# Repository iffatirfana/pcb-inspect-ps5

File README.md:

# Fabric Inspection Assistant (Raspberry Pi 5, fully offline)

Bharat AI-SoC Challenge 2026-27, Problem Statement 5: real-time industrial defect detection and quality-control assistant.
Entry: textile and fabric quality control on a Raspberry Pi 5 (CPU only), with Llama 3.2 1B running through ExecuTorch.

## What it does

One photo goes in; a verdict, a repair route and a short three-line operator note come out, with no cloud connection.

```
photo / webcam -> YOLOv8n-seg detector (onnxruntime) -> rule engine (severity, verdict)
              -> [only if nothing found] anomaly second opinion (ResNet18 + normal-patch bank)
              -> Llama 3.2 1B on ExecuTorch (Risk / Check / Action note) -> dashboard + SQLite log
```

- **Detector:** finds Hole, Knot, Line and Stain defects, with polygon and area.
- **Anomaly second opinion:** when the detector finds nothing, a second model compares the photo with a memory bank of normal-denim patches (ResNet18 layer2+layer3 features, nearest-neighbour distance, PatchCore-style). If more than 1.5% of the photo looks abnormal, the verdict becomes **REVIEW** with up to three regions marked "Anomaly". It can only raise PASS to REVIEW; it never causes REWORK or REJECT, and it does not run when the detector already found a defect. The dashboard shows an **anomaly heatmap** card (per-pixel score, flag threshold outlined) for these photos.
- **Rule engine:** Low / Medium / High severity from area, then PASS / REVIEW / REWORK / REJECT. Only rules decide the verdict.
- **Rule-generated recommendations:** disposition, urgency, repair route, what to check and likely cause per defect (`kb/fabric_guidance.yaml`).
- **Llama advisor:** writes three lines (Risk, Check, Action) from the verdict, findings and SOP line, using a ~300-token chat-template prompt with one worked example. Its reply is validated: it must not say release/ship/approve for a non-PASS verdict, and every number must come from the facts it was given. On any failure, after one retry, a template built from the SOP is used. Skipped on PASS.
- **Dashboard:** local web page with a colour verdict banner, annotated photo, findings table, recommendations, the Llama note, the anomaly heatmap when the second opinion fires, timings, operator feedback and history.
- **Log:** every inspection is stored in SQLite (`fabric_inspections`).

Vision runs on the Pi CPU (onnxruntime). Llama runs on the Arm CPU through ExecuTorch. No Hailo accelerator is used.

## Measured results (Raspberry Pi 5, 16 GB, our own photos of blue denim)

| Measurement | Value |
| --- | --- |
| Detector time | 583 ms (about 1.7 FPS, 960 px input) |
| Photo to verdict | 0.99 s median |
| Llama advice, persistent runner | 7 to 14 s per reply (16 tokens per second) |
| Peak memory | Python 226 MB + Llama runner 731 MB (0.96 GB of 16 GB) |
| False alarms at confidence 0.5 | 0 of 71 normal photos |
| Hole recall at confidence 0.5 | 12 of 15 |
| Thread (Line) recall at confidence 0.5, detector alone | 2 of 6 (weak) |

### Anomaly second opinion (held-out photos, same denim fabric)

The memory bank was built from the 51 train photos only. The pixel threshold was chosen on the 10 validation photos only. The test normals and all defect photos were never used for building or tuning. Run through the full pipeline (laptop CPU, about 0.38 s per photo):

| Set | Result |
| --- | --- |
| Validation normals (10) | 10 PASS (threshold set here) |
| Test normals (10) | 8 PASS, 2 REVIEW (false alarms) |
| Holes (15) | detector alone 12 REJECT; with second opinion 15 of 15 flagged (3 as REVIEW) |
| Threads (6) | detector alone 2 REJECT; with second opinion 6 of 6 flagged (4 as REVIEW) |

These are small sets from one fabric and one camera setup, so they show the idea works but are not an accuracy claim. On the Pi the anomaly step took about 0.76 s on a clean photo (full clean-photo run 1.11 s). Full pipeline, fresh process: hole photo REJECT with model-written advice in 5.09 s including model load; two consecutive requests to the persistent runner ran without reload.

## Pattern cloth: missing-motif check

`fabric_pattern.py` looks for a missing printed motif on repeating-print cloth (fabric key `pattern`). It finds the
print grid in one photo and flags a position that has a motif on both sides but almost no printed ink.
It needs no reference photo and never gives more than REVIEW.

| Test | Result |
|---|---|
| 30 synthetic missing motifs (made from normal photos) | 27 found at the right place |
| 14 clean photos not used to build the rule | 1 flagged (1 false gap) |

Limits: the missing motifs are synthetic and the clean photos show only a few cloth positions, so treat the
numbers as an estimate. Wrong-type or flipped motifs are not detected (the hand-printed motifs vary too much).
It works only on a regular repeating print. A reference-photo comparison was tried first and rejected: it
flagged 6 of 14 clean photos because the cloth layout differs between areas. A DINOv2 Siamese model from the
team was also tested; alone it flags too many regions on clean cloth, so it is not in the pipeline.

## Limitations

- The anomaly second opinion is trained on normal blue denim only and flags about 2 in 10 held-out normal photos for a quick manual check. It is advisory: it can raise PASS to REVIEW and nothing more.
- Trained on blue denim only. A yellow patterned cloth gave false Holes, and on grey cloth and in shadows the anomaly second opinion flags regions (REVIEW only); other fabrics need new data or a bank built from clean photos of that fabric.
- The pixel-to-mm scale in `kb/fabric.yaml` (`px_per_mm`) comes from a ruler photo and is valid only for that camera, height and image size; redo it if the setup changes. If `calibrated` is false the dashboard warns that sizes and severities are estimates.
- The older `..._512.pte` file measured only about 127 tokens of usable context on the Pi. The rebuilt `llama3_2_1b_q8da4w_ctx512.pte` was tested on the Pi with prompts of 7, 213 and 469 tokens (469 + 42 generated = 511). `config.yaml` caps prompt plus reply at 480 tokens; the advice prompt is about 300 tokens.
- Experiments that did not help (tiling, a larger 960x960 detector) are described in the technical report.

## Repository layout (fabric entry)

| Path | Purpose |
| --- | --- |
| `fabric_yolo.py` | onnxruntime-only YOLOv8-seg detector (letterbox, NMS, mask polygons) |
| `fabric_scorer.py` | ResNet18 feature extractor plus normal-patch bank, giving the anomaly heatmap (also drawn on the dashboard) |
| `fabric_profile.py` | detections to findings in mm, severity, verdict, Llama payload |
| `fabric_actions.py`, `kb/fabric_guidance.yaml` | rule-generated recommendation fields |
| `fabric_advisor.py` | prompt, validation, retry and template fallback for Llama |
| `fabric_pipeline.py` | capture, quality gate, detect, rules, advice, SQLite log; CLI and `--live` webcam mode |
| `ui/fabric_app.py` | offline operator dashboard |
| `llm/executorch_backend.py` | runs the `.pte` with the ExecuTorch `llama_main` runner (persistent server mode) |
| `tools/patch_llama_main_server.py` | adds `--server` mode to ExecuTorch's `llama_main` |
| `kb/fabric.yaml` | fabric settings, thresholds (including the anomaly pixel threshold and 1.5% rule), SOP text per verdict |
| `tests/` | unit tests |

## Run on a laptop (no Llama needed; a mock advisor is used)

```bash
python -m venv .venv
.venv/bin/pip install numpy opencv-python-headless pyyaml pydantic onnxruntime flask psutil pytest   # Windows: .venv\Scripts\pip
.venv/bin/python -m pytest tests/test_fabric_profile.py tests/test_fabric_actions.py tests/test_fabric_app.py tests/test_fabric_pipeline.py -q
.venv/bin/python fabric_pipeline.py blue path/to/photo.jpg
.venv/bin/python -m ui.fabric_app      # http://127.0.0.1:5000
```
This needs `models/best_169.onnx` (see Models below).

## Run on the Raspberry Pi 5

1. Flash Raspberry Pi OS (64-bit), enable SSH, clone this repository, create a virtual environment and run `pip install -r requirements.txt`. On the Pi the Python `executorch` package is not needed; the C++ runner is used.
2. Put the model files in `models/` (see Models).
3. Build ExecuTorch v1.5.1 and its Llama runner following `examples/models/llama/README.md` in the ExecuTorch repository. Apply `python tools/patch_llama_main_server.py` to `examples/models/llama/main.cpp`, then rebuild with `cmake --workflow --preset llama-release` from `examples/models/llama`. The runner is expected at `~/executorch/cmake-out/examples/models/llama/llama_main`.
4. Start the dashboard: `python -m ui.fabric_app`, then open `http://<pi-ip>:5000`.
5. Webcam: a USB camera at `/dev/video0` (MJPG 1920x1080) is used by the Capture button and by `python fabric_pipeline.py blue --live`.

## Models

Model files are not stored in Git except the detector and the two anomaly files (force-added because `.gitignore` excludes `*.onnx`).

| File | What | Source |
| --- | --- | --- |
| `models/best_169.onnx` (13.7 MB) | YOLOv8n-seg detector, 640x384 input | trained by the team on the public denim dataset below |
| `models/anomaly/resnet18_fused.onnx` (11 MB) | ResNet18 layer2+layer3 feature extractor, 512x512 input | ResNet18 ImageNet weights exported to ONNX by the team |
| `models/anomaly/bank_blue_trainonly.npy` (7.7 MB) | 5000 normal-denim patch features (384 values each) | built from the 51 training photos |
| `models/llama3_2_1b_q8da4w_ctx512.pte` (766 MB) | Llama 3.2 1B Instruct, ExecuTorch, 8da4w, XNNPACK | exported by the team with ExecuTorch 1.5.1 |
| `models/tokenizer.model` (2.2 MB) | Llama 3 tokenizer | from Llama 3.2 |

The Llama files are fetched with `llm.executorch_backend.download_models()` from the team's Hugging Face repository.

## Credits and licences

- Defect dataset: public denim defect dataset on Roboflow (workspace i-g-geethashri, project bkdn-huylv-datn-mt9s6, version 3), licence CC BY 4.0.
- Anomaly method: PatchCore-style nearest-neighbour patch scoring (Roth et al., "Towards Total Recall in Industrial Anomaly Detection", CVPR 2022); feature extractor ResNet18 with ImageNet weights (torchvision).
- YOLOv8 training used ultralytics (AGPL-3.0); inference in this repository uses onnxruntime only.
- Llama 3.2 1B: Meta, under the Llama 3.2 Community Licence. **Built with Llama.**
- ExecuTorch: PyTorch / Meta, BSD-style licence.
- Code in this repository: MIT.

## Team

Iffat Irfana M, I.G Geethashri and Harini V (detector, rule engine, Pi deployment, Llama stage, dashboard, anomaly detector). Faculty Mentor: Aathilakshmi, Associate Professor, ECE department.

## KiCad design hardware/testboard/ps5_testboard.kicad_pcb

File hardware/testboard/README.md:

# PS5 inspection test board v1

50 × 50 mm, 2-layer, 1.6 mm FR-4. Designed to produce every defect type in `kb/acceptance.yaml`.

## Circuit
5 V in (J1) → SS14 reverse protection (D6) → AMS1117-3.3 (U1) → 3V3.
74HC595 (U2, TSSOP-16) drives LEDs D1–D4; output QE switches power LED D5 through 2N7002 (Q1).
24C02 EEPROM (U3, SOIC-8) on I²C header J2. Shift-register inputs on J3.

## Status
| Item | State |
|---|---|
| Placement | Done – all SMD on top, pin-1 / polarity marks, 3 asymmetric fiducials, 4 × M3 holes |
| Routing | Done – autorouted (Freerouting), 0.5 mm power / 0.25 mm signal tracks |
| Ground | Pours on both layers + GND stitching vias |
| DRC | 0 clearance errors, 0 unconnected |

## Files
| File | Use |
|---|---|
| `ps5_testboard.kicad_pcb` | KiCad board (open in PCB Editor) |
| `fab/ps5_testboard_gerbers.zip` | Gerbers + drill – upload to the PCB fab |
| `fab/ps5_testboard_BOM.csv` | Bill of materials |
| `fab/ps5_testboard_CPL.csv` | Pick-and-place positions for SMT assembly (top side). J1–J3 are through-hole headers. |
| `ps5_testboard_routed.png` | Top (red) and bottom (blue) copper preview |

## Before ordering
1. Open the board in KiCad 10, press **B** (refill zones), run **Inspect → Design Rules Checker**.
2. Check pin 1 of U1/U2/U3/Q1 and the cathode marks of D1–D6 against the parts you buy.
3. Check the fab's assembly rotation conventions against `CPL.csv` in their online preview.

The board map used by the pipeline (`kb/board_demo/pos.csv`, `pads.csv`) is generated from this file:
`python -m tools.kicad_to_csv hardware/testboard/ps5_testboard.kicad_pcb kb/board_demo`

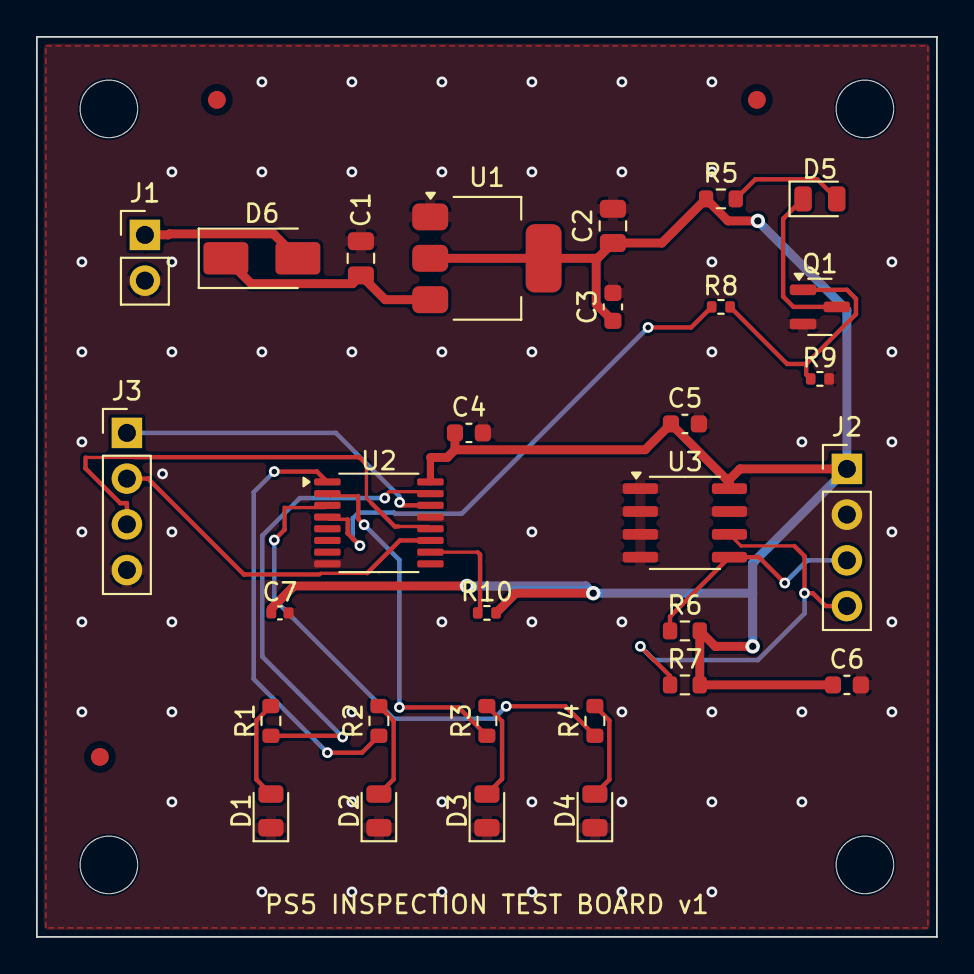
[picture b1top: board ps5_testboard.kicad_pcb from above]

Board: 2 copper layers, 50.0 x 50.0 mm, 37 parts (0 on the bottom side), 22 nets.

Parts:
C1, C2: 10uF; C_0805_2012Metric
C3, C4, C5, C6: 100nF; C_0603_1608Metric
C7: 100nF; C_0402_1005Metric
D1, D2, D3, D4: LED; LED_0805_2012Metric
D5: PWR; LED_0805_2012Metric
D6: SS14; D_SMA
FID1, FID2, FID3: FID; Fiducial_1mm_Mask2mm
H1, H2, H3, H4: M3; MountingHole_3.2mm_M3
J1: 5V IN; PinHeader_1x02_P2.54mm_Vertical
J2: I2C; PinHeader_1x04_P2.54mm_Vertical
J3: SHIFT; PinHeader_1x04_P2.54mm_Vertical
Q1: 2N7002; SOT-23
R1, R2, R3, R4, R5: 1k; R_0603_1608Metric
R6, R7: 4.7k; R_0603_1608Metric
R8: 100R; R_0402_1005Metric
R9, R10: 10k; R_0402_1005Metric
U1: AMS1117-3.3; SOT-223-3_TabPin2
U2: 74HC595; TSSOP-16_4.4x5mm_P0.65mm
U3: 24C02; SOIC-8_3.9x4.9mm_P1.27mm

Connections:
3V3: C2.1, C3.1, C4.1, C5.1, C6.1, C7.1, J2.1, R5.1, R6.2, R7.2, R10.2, U1.2, U2.16, U3.8
+5V: C1.1, D6.1, U1.3
+5V_IN: D6.2, J1.1
D5_K: D5.1, Q1.3
DS: J3.1, U2.14
GATE: Q1.1, R8.2, R9.1
GND: C1.2, C2.2, C3.2, C4.2, C5.2, C6.2, C7.2, D1.1, D2.1, D3.1, D4.1, J1.2, J2.2, J3.4, Q1.2, R9.2, U1.1, U2.8, U2.13, U3.1, U3.2, U3.3, U3.4, U3.7
LED1: D1.2, R1.2
LED2: D2.2, R2.2
LED3: D3.2, R3.2
LED4: D4.2, R4.2
LED5: D5.2, R5.2
MR_N: R10.1, U2.10
QA: R1.1, U2.15
QB: R2.1, U2.1
QC: R3.1, U2.2
QD: R4.1, U2.3
QE: R8.1, U2.4
SCL: J2.4, R7.1, U3.6
SDA: J2.3, R6.1, U3.5
SHCP: J3.2, U2.11
STCP: J3.3, U2.12

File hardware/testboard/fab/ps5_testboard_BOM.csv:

Qty,Value,Footprint,Designators
2,10uF,C_0805_2012Metric,C1 C2
4,100nF,C_0603_1608Metric,C3 C4 C5 C6
1,100nF,C_0402_1005Metric,C7
4,LED,LED_0805_2012Metric,D1 D2 D3 D4
1,PWR,LED_0805_2012Metric,D5
1,SS14,D_SMA,D6
1,5V IN,PinHeader_1x02_P2.54mm_Vertical,J1
1,I2C,PinHeader_1x04_P2.54mm_Vertical,J2
1,SHIFT,PinHeader_1x04_P2.54mm_Vertical,J3
1,2N7002,SOT-23,Q1
5,1k,R_0603_1608Metric,R1 R2 R3 R4 R5
2,4.7k,R_0603_1608Metric,R6 R7
1,100R,R_0402_1005Metric,R8
2,10k,R_0402_1005Metric,R9 R10
1,AMS1117-3.3,SOT-223-3_TabPin2,U1
1,74HC595,TSSOP-16_4.4x5mm_P0.65mm,U2
1,24C02,SOIC-8_3.9x4.9mm_P1.27mm,U3
